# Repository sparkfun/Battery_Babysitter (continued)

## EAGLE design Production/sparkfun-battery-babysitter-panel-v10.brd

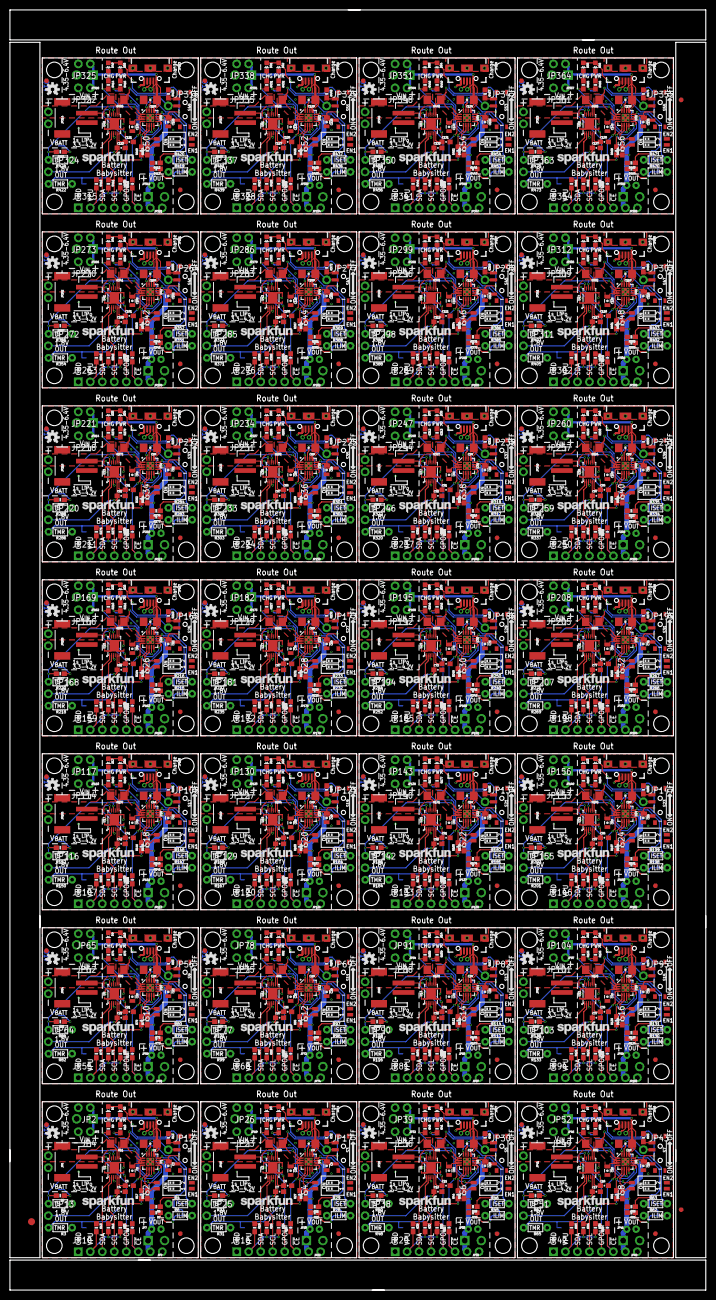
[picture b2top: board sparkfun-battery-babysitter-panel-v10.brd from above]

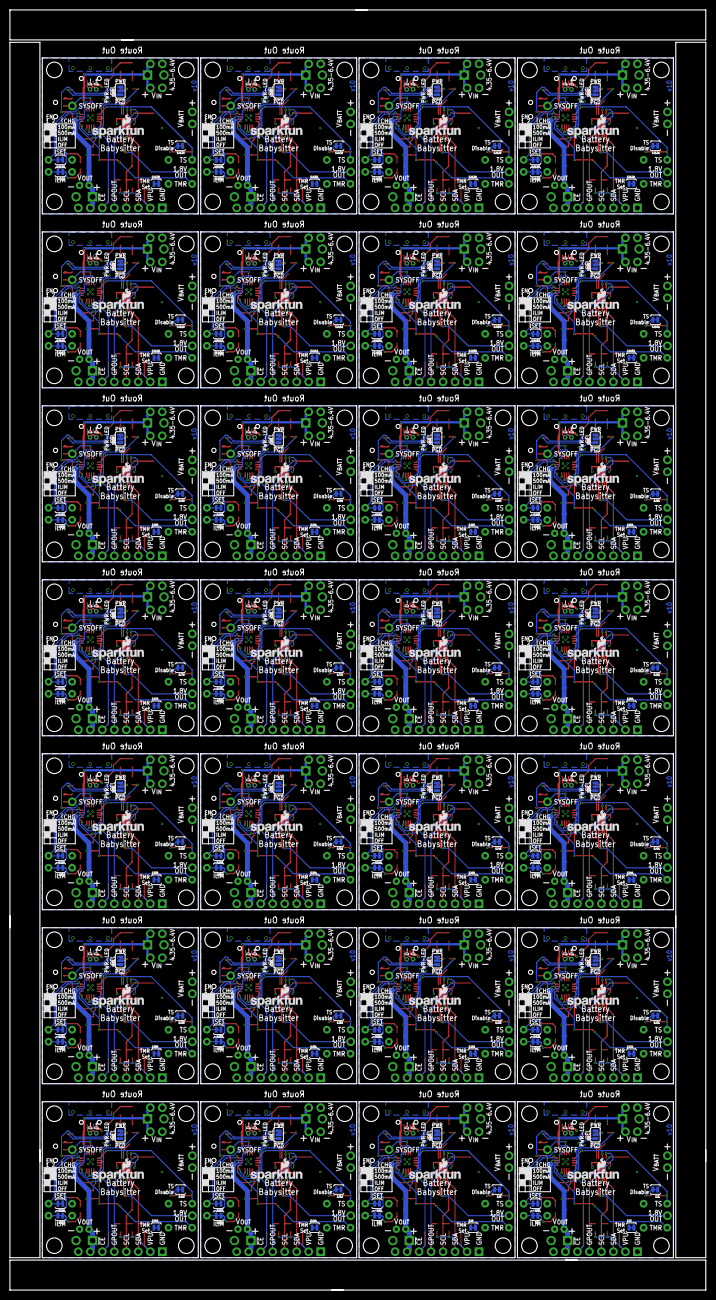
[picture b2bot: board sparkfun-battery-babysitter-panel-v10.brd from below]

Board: 2 copper layers, 147.3 x 271.0 mm, 1599 parts (224 on the bottom side), 840 nets.

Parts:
C1, C9, C14, C19, C24, C29, C34, C39, C44, C49, C54, C59, C64, C69, C74, C79, C84, C89, C94, C99, C104, C109, C114, C119, C124, C129, C134, C139: 1.0uF; 1206-CAP
C2, C3, C8, C10, C13, C15, C18, C20, C23, C25, C28, C30, C33, C35, C38, C40, C43, C45, C48, C50, C53, C55, C58, C60, C63, C65, C68, C70, C73, C75, C78, C80, C83, C85, C88, C90, C93, C95, C98, C100, C103, C105, C108, C110, C113, C115, C118, C120, C123, C125, C128, C130, C133, C135, C138, C140: 10uF; 0805-CAP
C4, C7, C12, C17, C22, C27, C32, C37, C42, C47, C52, C57, C62, C67, C72, C77, C82, C87, C92, C97, C102, C107, C112, C117, C122, C127, C132, C137: 0.47uF; 0603-CAP
C5, C6, C11, C16, C21, C26, C31, C36, C41, C46, C51, C56, C61, C66, C71, C76, C81, C86, C91, C96, C101, C106, C111, C116, C121, C126, C131, C136: 1.0uF; 0603-CAP
D1, D3, D5, D7, D9, D11, D13, D15, D17, D19, D21, D23, D25, D27, D29, D31, D33, D35, D37, D39, D41, D43, D45, D47, D49, D51, D53, D55: BLUE; LED-0603
D2, D4, D6, D8, D10, D12, D14, D16, D18, D20, D22, D24, D26, D28, D30, D32, D34, D36, D38, D40, D42, D44, D46, D48, D50, D52, D54, D56: RED; LED-0603
E$1: FIDUCIAL-1.5X3
E$5, E$6: FIDUCIAL-1X2
FID1, FID2, FID3, FID4, FID5, FID6, FID7, FID8, FID9, FID10, FID11, FID12, FID13, FID14, FID15, FID16, FID17, FID18, FID19, FID20, FID21, FID22, FID23, FID24, FID25, FID26, FID27, FID28, FID29, FID30, FID31, FID32, FID33, FID34, FID35, FID36, FID37, FID38, FID39, FID40, FID41, FID42, FID43, FID44, FID45, FID46, FID47, FID48, FID49, FID50, FID51, FID52, FID53, FID54, FID55, FID56: FIDUCIAL1X2; FIDUCIAL-1X2
JP1, JP14, JP27, JP40, JP53, JP66, JP79, JP92, JP105, JP118, JP131, JP144, JP157, JP170, JP183, JP196, JP209, JP222, JP235, JP248, JP261, JP274, JP287, JP300, JP313, JP326, JP339, JP352: USB-AB-MICRO-SMD_V03
JP2, JP4, JP5, JP8, JP11, JP18, JP21, JP23, JP24, JP26, JP31, JP34, JP36, JP37, JP39, JP44, JP47, JP49, JP50, JP52, JP57, JP60, JP62, JP63, JP65, JP70, JP73, JP75, JP76, JP78, JP83, JP86, JP88, JP89, JP91, JP96, JP99, JP101, JP102, JP104, JP109, JP112, JP114, JP115, JP117, JP122, JP125, JP127, JP128, JP130, JP135, JP138, JP140, JP141, JP143, JP148, JP151, JP153, JP154, JP156, JP161, JP164, JP166, JP167, JP169, JP174, JP177, JP179, JP180, JP182, JP187, JP190, JP192, JP193, JP195, JP200, JP203, JP205, JP206, JP208, JP213, JP216, JP218, JP219, JP221, JP226, JP229, JP231, JP232, JP234, JP239, JP242, JP244, JP245, JP247, JP252, JP255, JP257, JP258, JP260, JP265, JP268, JP270, JP271, JP273, JP278, JP281, JP283, JP284, JP286, JP291, JP294, JP296, JP297, JP299, JP304, JP307, JP309, JP310, JP312, JP317, JP320, JP322, JP323, JP325, JP330, JP333, JP335, JP336, JP338, JP343, JP346, JP348, JP349, JP351, JP356, JP359, JP361, JP362, JP364: 1X02_NO_SILK
JP3, JP7, JP19, JP20, JP32, JP33, JP45, JP46, JP58, JP59, JP71, JP72, JP84, JP85, JP97, JP98, JP110, JP111, JP123, JP124, JP136, JP137, JP149, JP150, JP162, JP163, JP175, JP176, JP188, JP189, JP201, JP202, JP214, JP215, JP227, JP228, JP240, JP241, JP253, JP254, JP266, JP267, JP279, JP280, JP292, JP293, JP305, JP306, JP318, JP319, JP331, JP332, JP344, JP345, JP357, JP358: SCREWTERMINAL-3.5MM-2-NS
JP6, JP15, JP28, JP41, JP54, JP67, JP80, JP93, JP106, JP119, JP132, JP145, JP158, JP171, JP184, JP197, JP210, JP223, JP236, JP249, JP262, JP275, JP288, JP301, JP314, JP327, JP340, JP353: JST-2-SMD
JP9, JP22, JP35, JP48, JP61, JP74, JP87, JP100, JP113, JP126, JP139, JP152, JP165, JP178, JP191, JP204, JP217, JP230, JP243, JP256, JP269, JP282, JP295, JP308, JP321, JP334, JP347, JP360: JST-2-PTH-NS
JP10, JP16, JP29, JP42, JP55, JP68, JP81, JP94, JP107, JP120, JP133, JP146, JP159, JP172, JP185, JP198, JP211, JP224, JP237, JP250, JP263, JP276, JP289, JP302, JP315, JP328, JP341, JP354: 1X04_NO_SILK
JP12, JP13, JP17, JP25, JP30, JP38, JP43, JP51, JP56, JP64, JP69, JP77, JP82, JP90, JP95, JP103, JP108, JP116, JP121, JP129, JP134, JP142, JP147, JP155, JP160, JP168, JP173, JP181, JP186, JP194, JP199, JP207, JP212, JP220, JP225, JP233, JP238, JP246, JP251, JP259, JP264, JP272, JP277, JP285, JP290, JP298, JP303, JP311, JP316, JP324, JP329, JP337, JP342, JP350, JP355, JP363: 1X01_NO_SILK
LOGO1, LOGO4, LOGO7, LOGO10, LOGO13, LOGO16, LOGO19, LOGO22, LOGO25, LOGO28, LOGO31, LOGO34, LOGO37, LOGO40, LOGO43, LOGO46, LOGO49, LOGO52, LOGO55, LOGO58, LOGO61, LOGO64, LOGO67, LOGO70, LOGO73, LOGO76, LOGO79, LOGO82: SFE_LOGO_NAME.1_INCH; SFE_LOGO_NAME_.1
LOGO2, LOGO6, LOGO9, LOGO12, LOGO15, LOGO18, LOGO21, LOGO24, LOGO27, LOGO30, LOGO33, LOGO36, LOGO39, LOGO42, LOGO45, LOGO48, LOGO51, LOGO54, LOGO57, LOGO60, LOGO63, LOGO66, LOGO69, LOGO72, LOGO75, LOGO78, LOGO81, LOGO84: SFE_LOGO_NAME_FLAME.1_INCH; SFE_LOGO_NAME_FLAME_.1
LOGO3, LOGO5, LOGO8, LOGO11, LOGO14, LOGO17, LOGO20, LOGO23, LOGO26, LOGO29, LOGO32, LOGO35, LOGO38, LOGO41, LOGO44, LOGO47, LOGO50, LOGO53, LOGO56, LOGO59, LOGO62, LOGO65, LOGO68, LOGO71, LOGO74, LOGO77, LOGO80, LOGO83: OSHW-LOGOS; OSHW-LOGO-S
R1, R33, R50, R67, R84, R101, R118, R135, R152, R169, R186, R203, R220, R237, R254, R271, R288, R305, R322, R339, R356, R373, R390, R407, R424, R441, R458, R475: TS; 1/6W-RES
R2, R15, R16, R17, R26, R27, R30, R34, R43, R44, R47, R51, R60, R61, R64, R68, R77, R78, R81, R85, R94, R95, R98, R102, R111, R112, R115, R119, R128, R129, R132, R136, R145, R146, R149, R153, R162, R163, R166, R170, R179, R180, R183, R187, R196, R197, R200, R204, R213, R214, R217, R221, R230, R231, R234, R238, R247, R248, R251, R255, R264, R265, R268, R272, R281, R282, R285, R289, R298, R299, R302, R306, R315, R316, R319, R323, R332, R333, R336, R340, R349, R350, R353, R357, R366, R367, R370, R374, R383, R384, R387, R391, R400, R401, R404, R408, R417, R418, R421, R425, R434, R435, R438, R442, R451, R452, R455, R459, R468, R469, R472, R476: 10K; 0603-RES
R3, R31, R48, R65, R82, R99, R116, R133, R150, R167, R184, R201, R218, R235, R252, R269, R286, R303, R320, R337, R354, R371, R388, R405, R422, R439, R456, R473: TMR; 1/6W-RES
R4, R29, R46, R63, R80, R97, R114, R131, R148, R165, R182, R199, R216, R233, R250, R267, R284, R301, R318, R335, R352, R369, R386, R403, R420, R437, R454, R471: ISET; 1/6W-RES
R5, R21, R38, R55, R72, R89, R106, R123, R140, R157, R174, R191, R208, R225, R242, R259, R276, R293, R310, R327, R344, R361, R378, R395, R412, R429, R446, R463: 590; 0603-RES
R6, R28, R45, R62, R79, R96, R113, R130, R147, R164, R181, R198, R215, R232, R249, R266, R283, R300, R317, R334, R351, R368, R385, R402, R419, R436, R453, R470: ILIM; 1/6W-RES
R7, R22, R39, R56, R73, R90, R107, R124, R141, R158, R175, R192, R209, R226, R243, R260, R277, R294, R311, R328, R345, R362, R379, R396, R413, R430, R447, R464: 1.1k; 0603-RES
R8, R12, R25, R32, R42, R49, R59, R66, R76, R83, R93, R100, R110, R117, R127, R134, R144, R151, R161, R168, R178, R185, R195, R202, R212, R219, R229, R236, R246, R253, R263, R270, R280, R287, R297, R304, R314, R321, R331, R338, R348, R355, R365, R372, R382, R389, R399, R406, R416, R423, R433, R440, R450, R457, R467, R474: 100k; 0603-RES
R9, R23, R40, R57, R74, R91, R108, R125, R142, R159, R176, R193, R210, R227, R244, R261, R278, R295, R312, R329, R346, R363, R380, R397, R414, R431, R448, R465: 180; 0603-RES
R10, R24, R41, R58, R75, R92, R109, R126, R143, R160, R177, R194, R211, R228, R245, R262, R279, R296, R313, R330, R347, R364, R381, R398, R415, R432, R449, R466: 1K; 0603-RES
R11, R18, R35, R52, R69, R86, R103, R120, R137, R154, R171, R188, R205, R222, R239, R256, R273, R290, R307, R324, R341, R358, R375, R392, R409, R426, R443, R460: 0.01; 1206
R13, R14, R19, R20, R36, R37, R53, R54, R70, R71, R87, R88, R104, R105, R121, R122, R138, R139, R155, R156, R172, R173, R189, R190, R206, R207, R223, R224, R240, R241, R257, R258, R274, R275, R291, R292, R308, R309, R325, R326, R342, R343, R359, R360, R376, R377, R393, R394, R410, R411, R427, R428, R444, R445, R461, R462: 4.7K; 0603-RES
S1, S3, S5, S7, S9, S11, S13, S15, S17, S19, S21, S23, S25, S27, S29, S31, S33, S35, S37, S39, S41, S43, S45, S47, S49, S51, S53, S55: SWITCH-SPST-SMD-A
S2, S4, S6, S8, S10, S12, S14, S16, S18, S20, S22, S24, S26, S28, S30, S32, S34, S36, S38, S40, S42, S44, S46, S48, S50, S52, S54, S56: DIPSWITCH-02-50MIL
SJ1, SJ2, SJ3, SJ4, SJ6, SJ7, SJ8, SJ9, SJ11, SJ12, SJ13, SJ14, SJ16, SJ17, SJ18, SJ19, SJ21, SJ22, SJ23, SJ24, SJ26, SJ27, SJ28, SJ29, SJ31, SJ32, SJ33, SJ34, SJ36, SJ37, SJ38, SJ39, SJ41, SJ42, SJ43, SJ44, SJ46, SJ47, SJ48, SJ49, SJ51, SJ52, SJ53, SJ54, SJ56, SJ57, SJ58, SJ59, SJ61, SJ62, SJ63, SJ64, SJ66, SJ67, SJ68, SJ69, SJ71, SJ72, SJ73, SJ74, SJ76, SJ77, SJ78, SJ79, SJ81, SJ82, SJ83, SJ84, SJ86, SJ87, SJ88, SJ89, SJ91, SJ92, SJ93, SJ94, SJ96, SJ97, SJ98, SJ99, SJ101, SJ102, SJ103, SJ104, SJ106, SJ107, SJ108, SJ109, SJ111, SJ112, SJ113, SJ114, SJ116, SJ117, SJ118, SJ119, SJ121, SJ122, SJ123, SJ124, SJ126, SJ127, SJ128, SJ129, SJ131, SJ132, SJ133, SJ134, SJ136, SJ137, SJ138, SJ139: PAD-JUMPER-2-NC_BY_TRACE_YES_SILK
SJ5, SJ10, SJ15, SJ20, SJ25, SJ30, SJ35, SJ40, SJ45, SJ50, SJ55, SJ60, SJ65, SJ70, SJ75, SJ80, SJ85, SJ90, SJ95, SJ100, SJ105, SJ110, SJ115, SJ120, SJ125, SJ130, SJ135, SJ140: PAD-JUMPER-3-2OF3_NC_BY_TRACE_YES_SILK_FULL_BOX
STANDOFF1, STANDOFF2, STANDOFF3, STANDOFF4, STANDOFF5, STANDOFF6, STANDOFF7, STANDOFF8, STANDOFF9, STANDOFF10, STANDOFF11, STANDOFF12, STANDOFF13, STANDOFF14, STANDOFF15, STANDOFF16, STANDOFF17, STANDOFF18, STANDOFF19, STANDOFF20, STANDOFF21, STANDOFF22, STANDOFF23, STANDOFF24, STANDOFF25, STANDOFF26, STANDOFF27, STANDOFF28, STANDOFF29, STANDOFF30, STANDOFF31, STANDOFF32, STANDOFF33, STANDOFF34, STANDOFF35, STANDOFF36, STANDOFF37, STANDOFF38, STANDOFF39, STANDOFF40, STANDOFF41, STANDOFF42, STANDOFF43, STANDOFF44, STANDOFF45, STANDOFF46, STANDOFF47, STANDOFF48, STANDOFF49, STANDOFF50, STANDOFF51, STANDOFF52, STANDOFF53, STANDOFF54, STANDOFF55, STANDOFF56, STANDOFF57, STANDOFF58, STANDOFF59, STANDOFF60, STANDOFF61, STANDOFF62, STANDOFF63, STANDOFF64, STANDOFF65, STANDOFF66, STANDOFF67, STANDOFF68, STANDOFF69, STANDOFF70, STANDOFF71, STANDOFF72, STANDOFF73, STANDOFF74, STANDOFF75, STANDOFF76, STANDOFF77, STANDOFF78, STANDOFF79, STANDOFF80, STANDOFF81, STANDOFF82, STANDOFF83, STANDOFF84, STANDOFF85, STANDOFF86, STANDOFF87, STANDOFF88, STANDOFF89, STANDOFF90, STANDOFF91, STANDOFF92, STANDOFF93, STANDOFF94, STANDOFF95, STANDOFF96, STANDOFF97, STANDOFF98, STANDOFF99, STANDOFF100, STANDOFF101, STANDOFF102, STANDOFF103, STANDOFF104, STANDOFF105, STANDOFF106, STANDOFF107, STANDOFF108, STANDOFF109, STANDOFF110, STANDOFF111, STANDOFF112: STAND-OFF
TP1, TP2, TP3, TP4, TP5, TP6, TP7, TP8, TP9, TP10, TP11, TP12, TP13, TP14, TP15, TP16, TP17, TP18, TP19, TP20, TP21, TP22, TP23, TP24, TP25, TP26, TP27, TP28, TP29, TP30, TP31, TP32, TP33, TP34, TP35, TP36, TP37, TP38, TP39, TP40, TP41, TP42, TP43, TP44, TP45, TP46, TP47, TP48, TP49, TP50, TP51, TP52, TP53, TP54, TP55, TP56: PAD.03X.04
U1, U4, U6, U8, U10, U12, U14, U16, U18, U20, U22, U24, U26, U28, U30, U32, U34, U36, U38, U40, U42, U44, U46, U48, U50, U52, U54, U56: BQ24075; PVQFN-N16
U2, U3, U5, U7, U9, U11, U13, U15, U17, U19, U21, U23, U25, U27, U29, U31, U33, U35, U37, U39, U41, U43, U45, U47, U49, U51, U53, U55: BQ27441-G1; PDSO-N12

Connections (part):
1.8V: C4.1, JP13.1, U2.5
1.8V1: C7.1, JP25.1, U3.5
1.8V2: C12.1, JP38.1, U5.5
1.8V3: C17.1, JP51.1, U7.5
1.8V4: C22.1, JP64.1, U9.5
1.8V5: C27.1, JP77.1, U11.5
1.8V6: C32.1, JP90.1, U13.5
1.8V7: C37.1, JP103.1, U15.5
1.8V8: C42.1, JP116.1, U17.5
1.8V9: C47.1, JP129.1, U19.5
1.8V10: C52.1, JP142.1, U21.5
1.8V11: C57.1, JP155.1, U23.5
1.8V12: C62.1, JP168.1, U25.5
1.8V13: C67.1, JP181.1, U27.5
1.8V14: C72.1, JP194.1, U29.5
1.8V15: C77.1, JP207.1, U31.5
1.8V16: C82.1, JP220.1, U33.5
1.8V17: C87.1, JP233.1, U35.5
1.8V18: C92.1, JP246.1, U37.5
1.8V19: C97.1, JP259.1, U39.5
1.8V20: C102.1, JP272.1, U41.5
1.8V21: C107.1, JP285.1, U43.5
1.8V22: C112.1, JP298.1, U45.5
1.8V23: C117.1, JP311.1, U47.5
1.8V24: C122.1, JP324.1, U49.5
1.8V25: C127.1, JP337.1, U51.5
1.8V26: C132.1, JP350.1, U53.5
1.8V27: C137.1, JP363.1, U55.5
!CE!: JP11.1, R8.1, U1.4
!CE!1: JP24.1, R25.1, U4.4
!CE!2: JP37.1, R42.1, U6.4
!CE!3: JP50.1, R59.1, U8.4
!CE!4: JP63.1, R76.1, U10.4
!CE!5: JP76.1, R93.1, U12.4
!CE!6: JP89.1, R110.1, U14.4
!CE!7: JP102.1, R127.1, U16.4
!CE!8: JP115.1, R144.1, U18.4
!CE!9: JP128.1, R161.1, U20.4
!CE!10: JP141.1, R178.1, U22.4
!CE!11: JP154.1, R195.1, U24.4
!CE!12: JP167.1, R212.1, U26.4
!CE!13: JP180.1, R229.1, U28.4
!CE!14: JP193.1, R246.1, U30.4
!CE!15: JP206.1, R263.1, U32.4
!CE!16: JP219.1, R280.1, U34.4
!CE!17: JP232.1, R297.1, U36.4
!CE!18: JP245.1, R314.1, U38.4
!CE!19: JP258.1, R331.1, U40.4
!CE!20: JP271.1, R348.1, U42.4
!CE!21: JP284.1, R365.1, U44.4
!CE!22: JP297.1, R382.1, U46.4
!CE!23: JP310.1, R399.1, U48.4
!CE!24: JP323.1, R416.1, U50.4
!CE!25: JP336.1, R433.1, U52.4
!CE!26: JP349.1, R450.1, U54.4
!CE!27: JP362.1, R467.1, U56.4
!CHG!: R9.2, U1.9
!CHG!1: R23.2, U4.9
!CHG!2: R40.2, U6.9
!CHG!3: R57.2, U8.9
!CHG!4: R74.2, U10.9
!CHG!5: R91.2, U12.9
!CHG!6: R108.2, U14.9
!CHG!7: R125.2, U16.9
!CHG!8: R142.2, U18.9
!CHG!9: R159.2, U20.9
!CHG!10: R176.2, U22.9
!CHG!11: R193.2, U24.9
!CHG!12: R210.2, U26.9
!CHG!13: R227.2, U28.9
!CHG!14: R244.2, U30.9
!CHG!15: R261.2, U32.9
!CHG!16: R278.2, U34.9
!CHG!17: R295.2, U36.9
!CHG!18: R312.2, U38.9
!CHG!19: R329.2, U40.9
!CHG!20: R346.2, U42.9
!CHG!21: R363.2, U44.9
!CHG!22: R380.2, U46.9
!CHG!23: R397.2, U48.9
!CHG!24: R414.2, U50.9
!CHG!25: R431.2, U52.9
!CHG!26: R448.2, U54.9
!CHG!27: R465.2, U56.9
!PGOOD!: SJ5.1, U1.7
!PGOOD!1: SJ10.1, U4.7
!PGOOD!2: SJ15.1, U6.7
!PGOOD!3: SJ20.1, U8.7
!PGOOD!4: SJ25.1, U10.7
!PGOOD!5: SJ30.1, U12.7
!PGOOD!6: SJ35.1, U14.7
!PGOOD!7: SJ40.1, U16.7
!PGOOD!8: SJ45.1, U18.7
!PGOOD!9: SJ50.1, U20.7
!PGOOD!10: SJ55.1, U22.7
!PGOOD!11: SJ60.1, U24.7
!PGOOD!12: SJ65.1, U26.7
!PGOOD!13: SJ70.1, U28.7
!PGOOD!14: SJ75.1, U30.7
!PGOOD!15: SJ80.1, U32.7
!PGOOD!16: SJ85.1, U34.7
!PGOOD!17: SJ90.1, U36.7
!PGOOD!18: SJ95.1, U38.7
!PGOOD!19: SJ100.1, U40.7
!PGOOD!20: SJ105.1, U42.7
!PGOOD!21: SJ110.1, U44.7
!PGOOD!22: SJ115.1, U46.7
!PGOOD!23: SJ120.1, U48.7
!PGOOD!24: SJ125.1, U50.7
!PGOOD!25: SJ130.1, U52.7
!PGOOD!26: SJ135.1, U54.7
!PGOOD!27: SJ140.1, U56.7
BATTERY_IN: C5.1, JP5.2, JP6.2, R11.2, U2.6, U2.8
BATTERY_IN1: C6.1, JP15.2, JP18.2, R18.2, U3.6, U3.8
BATTERY_IN2: C11.1, JP28.2, JP31.2, R35.2, U5.6, U5.8
BATTERY_IN3: C16.1, JP41.2, JP44.2, R52.2, U7.6, U7.8
BATTERY_IN4: C21.1, JP54.2, JP57.2, R69.2, U9.6, U9.8
BATTERY_IN5: C26.1, JP67.2, JP70.2, R86.2, U11.6, U11.8
BATTERY_IN6: C31.1, JP80.2, JP83.2, R103.2, U13.6, U13.8
BATTERY_IN7: C36.1, JP93.2, JP96.2, R120.2, U15.6, U15.8
BATTERY_IN8: C41.1, JP106.2, JP109.2, R137.2, U17.6, U17.8
BATTERY_IN9: C46.1, JP119.2, JP122.2, R154.2, U19.6, U19.8
BATTERY_IN10: C51.1, JP132.2, JP135.2, R171.2, U21.6, U21.8
BATTERY_IN11: C56.1, JP145.2, JP148.2, R188.2, U23.6, U23.8
BATTERY_IN12: C61.1, JP158.2, JP161.2, R205.2, U25.6, U25.8
BATTERY_IN13: C66.1, JP171.2, JP174.2, R222.2, U27.6, U27.8
BATTERY_IN14: C71.1, JP184.2, JP187.2, R239.2, U29.6, U29.8
BATTERY_IN15: C76.1, JP197.2, JP200.2, R256.2, U31.6, U31.8
BATTERY_IN16: C81.1, JP210.2, JP213.2, R273.2, U33.6, U33.8
BATTERY_IN17: C86.1, JP223.2, JP226.2, R290.2, U35.6, U35.8
BATTERY_IN18: C91.1, JP236.2, JP239.2, R307.2, U37.6, U37.8
BATTERY_IN19: C96.1, JP249.2, JP252.2, R324.2, U39.6, U39.8
BATTERY_IN20: C101.1, JP262.2, JP265.2, R341.2, U41.6, U41.8
BATTERY_IN21: C106.1, JP275.2, JP278.2, R358.2, U43.6, U43.8
BATTERY_IN22: C111.1, JP288.2, JP291.2, R375.2, U45.6, U45.8
BATTERY_IN23: C116.1, JP301.2, JP304.2, R392.2, U47.6, U47.8
BATTERY_IN24: C121.1, JP314.2, JP317.2, R409.2, U49.6, U49.8
BATTERY_IN25: C126.1, JP327.2, JP330.2, R426.2, U51.6, U51.8
BATTERY_IN26: C131.1, JP340.2, JP343.2, R443.2, U53.6, U53.8
BATTERY_IN27: C136.1, JP353.2, JP356.2, R460.2, U55.6, U55.8
D+: JP1.D+1, TP2.P$1
D+1: JP14.D+1, TP4.P$1
D+2: JP27.D+1, TP6.P$1
D+3: JP40.D+1, TP8.P$1
D+4: JP53.D+1, TP10.P$1
D+5: JP66.D+1, TP12.P$1
D+6: JP79.D+1, TP14.P$1
D+7: JP92.D+1, TP16.P$1
D+8: JP105.D+1, TP18.P$1
D+9: JP118.D+1, TP20.P$1
D+10: JP131.D+1, TP22.P$1
D+11: JP144.D+1, TP24.P$1
D+12: JP157.D+1, TP26.P$1
D+13: JP170.D+1, TP28.P$1
D+14: JP183.D+1, TP30.P$1
D+15: JP196.D+1, TP32.P$1
D+16: JP209.D+1, TP34.P$1
D+17: JP222.D+1, TP36.P$1
D+18: JP235.D+1, TP38.P$1
D+19: JP248.D+1, TP40.P$1
D+20: JP261.D+1, TP42.P$1
D+21: JP274.D+1, TP44.P$1
D+22: JP287.D+1, TP46.P$1
D+23: JP300.D+1, TP48.P$1
D+24: JP313.D+1, TP50.P$1
D+25: JP326.D+1, TP52.P$1
D+26: JP339.D+1, TP54.P$1
D+27: JP352.D+1, TP56.P$1
D-: JP1.D-1, TP1.P$1
D-1: JP14.D-1, TP3.P$1
D-2: JP27.D-1, TP5.P$1
D-3: JP40.D-1, TP7.P$1
D-4: JP53.D-1, TP9.P$1
D-5: JP66.D-1, TP11.P$1
D-6: JP79.D-1, TP13.P$1
D-7: JP92.D-1, TP15.P$1
D-8: JP105.D-1, TP17.P$1
D-9: JP118.D-1, TP19.P$1
D-10: JP131.D-1, TP21.P$1
D-11: JP144.D-1, TP23.P$1
D-12: JP157.D-1, TP25.P$1
D-13: JP170.D-1, TP27.P$1
D-14: JP183.D-1, TP29.P$1
D-15: JP196.D-1, TP31.P$1
D-16: JP209.D-1, TP33.P$1
D-17: JP222.D-1, TP35.P$1
D-18: JP235.D-1, TP37.P$1
D-19: JP248.D-1, TP39.P$1
D-20: JP261.D-1, TP41.P$1
D-21: JP274.D-1, TP43.P$1
D-22: JP287.D-1, TP45.P$1
D-23: JP300.D-1, TP47.P$1
D-24: JP313.D-1, TP49.P$1
D-25: JP326.D-1, TP51.P$1
D-26: JP339.D-1, TP53.P$1
D-27: JP352.D-1, TP55.P$1
EN1: R16.2, S2.4, U1.6
EN2: R17.2, S2.3, U1.5
EN3: R27.2, S4.3, U4.5
EN4: R26.2, S4.4, U4.6
EN5: R44.2, S6.3, U6.5
EN6: R43.2, S6.4, U6.6
EN7: R61.2, S8.3, U8.5
EN8: R60.2, S8.4, U8.6
EN9: R78.2, S10.3, U10.5
EN10: R77.2, S10.4, U10.6
EN11: R95.2, S12.3, U12.5
EN12: R94.2, S12.4, U12.6
EN13: R112.2, S14.3, U14.5
EN14: R111.2, S14.4, U14.6
EN15: R129.2, S16.3, U16.5
EN16: R128.2, S16.4, U16.6
EN17: R146.2, S18.3, U18.5
EN18: R145.2, S18.4, U18.6
EN19: R163.2, S20.3, U20.5
EN20: R162.2, S20.4, U20.6
EN21: R180.2, S22.3, U22.5
EN22: R179.2, S22.4, U22.6
EN23: R197.2, S24.3, U24.5
EN24: R196.2, S24.4, U24.6
EN25: R214.2, S26.3, U26.5
EN26: R213.2, S26.4, U26.6
EN27: R231.2, S28.3, U28.5
EN28: R230.2, S28.4, U28.6
EN29: R248.2, S30.3, U30.5
EN30: R247.2, S30.4, U30.6
EN31: R265.2, S32.3, U32.5
EN32: R264.2, S32.4, U32.6
EN33: R282.2, S34.3, U34.5
EN34: R281.2, S34.4, U34.6
EN35: R299.2, S36.3, U36.5
EN36: R298.2, S36.4, U36.6
EN37: R316.2, S38.3, U38.5
EN38: R315.2, S38.4, U38.6
EN39: R333.2, S40.3, U40.5
EN40: R332.2, S40.4, U40.6
EN41: R350.2, S42.3, U42.5
EN42: R349.2, S42.4, U42.6
EN43: R367.2, S44.3, U44.5
EN44: R366.2, S44.4, U44.6
EN45: R384.2, S46.3, U46.5
EN46: R383.2, S46.4, U46.6
EN47: R401.2, S48.3, U48.5
EN48: R400.2, S48.4, U48.6
EN49: R418.2, S50.3, U50.5
EN50: R417.2, S50.4, U50.6
EN51: R435.2, S52.3, U52.5
EN52: R434.2, S52.4, U52.6
EN53: R452.2, S54.3, U54.5
EN54: R451.2, S54.4, U54.6
EN55: R469.2, S56.3, U56.5
EN56: R468.2, S56.4, U56.6
GND: C1.2, C2.2, C3.2, C4.2, C5.2, JP1.GND1, JP2.2, JP3.2, JP4.2, JP5.1, JP6.1, JP7.2, JP8.1, JP9.1, JP10.1, R1.1, R3.1, R4.1, R5.2, R6.1, R7.2, R8.2, S1.3, S2.1, S2.2, SJ1.1, SJ2.1, SJ5.3, U1.8, U1.EP, U2.3, U2.EP, U2.EP1, U2.EP2, U2.EP3, U2.EP4
GND1: C6.2, C7.2, C8.2, C9.2, C10.2, JP14.GND1, JP15.1, JP16.1, JP18.1, JP19.2, JP20.2, JP21.1, JP22.1, JP23.2, JP26.2, R21.2, R22.2, R25.2, R28.1, R29.1, R31.1, R33.1, S3.3, S4.1, S4.2, SJ6.1, SJ9.1, SJ10.3, U3.3, U3.EP, U3.EP1, U3.EP2, U3.EP3, U3.EP4, U4.8, U4.EP
GND2: C11.2, C12.2, C13.2, C14.2, C15.2, JP27.GND1, JP28.1, JP29.1, JP31.1, JP32.2, JP33.2, JP34.1, JP35.1, JP36.2, JP39.2, R38.2, R39.2, R42.2, R45.1, R46.1, R48.1, R50.1, S5.3, S6.1, S6.2, SJ11.1, SJ14.1, SJ15.3, U5.3, U5.EP, U5.EP1, U5.EP2, U5.EP3, U5.EP4, U6.8, U6.EP
GND3: C16.2, C17.2, C18.2, C19.2, C20.2, JP40.GND1, JP41.1, JP42.1, JP44.1, JP45.2, JP46.2, JP47.1, JP48.1, JP49.2, JP52.2, R55.2, R56.2, R59.2, R62.1, R63.1, R65.1, R67.1, S7.3, S8.1, S8.2, SJ16.1, SJ19.1, SJ20.3, U7.3, U7.EP, U7.EP1, U7.EP2, U7.EP3, U7.EP4, U8.8, U8.EP
GND4: C21.2, C22.2, C23.2, C24.2, C25.2, JP53.GND1, JP54.1, JP55.1, JP57.1, JP58.2, JP59.2, JP60.1, JP61.1, JP62.2, JP65.2, R72.2, R73.2, R76.2, R79.1, R80.1, R82.1, R84.1, S9.3, S10.1, S10.2, SJ21.1, SJ24.1, SJ25.3, U9.3, U9.EP, U9.EP1, U9.EP2, U9.EP3, U9.EP4, U10.8, U10.EP
GND5: C26.2, C27.2, C28.2, C29.2, C30.2, JP66.GND1, JP67.1, JP68.1, JP70.1, JP71.2, JP72.2, JP73.1, JP74.1, JP75.2, JP78.2, R89.2, R90.2, R93.2, R96.1, R97.1, R99.1, R101.1, S11.3, S12.1, S12.2, SJ26.1, SJ29.1, SJ30.3, U11.3, U11.EP, U11.EP1, U11.EP2, U11.EP3, U11.EP4, U12.8, U12.EP
GND6: C31.2, C32.2, C33.2, C34.2, C35.2, JP79.GND1, JP80.1, JP81.1, JP83.1, JP84.2, JP85.2, JP86.1, JP87.1, JP88.2, JP91.2, R106.2, R107.2, R110.2, R113.1, R114.1, R116.1, R118.1, S13.3, S14.1, S14.2, SJ31.1, SJ34.1, SJ35.3, U13.3, U13.EP, U13.EP1, U13.EP2, U13.EP3, U13.EP4, U14.8, U14.EP
GND7: C36.2, C37.2, C38.2, C39.2, C40.2, JP92.GND1, JP93.1, JP94.1, JP96.1, JP97.2, JP98.2, JP99.1, JP100.1, JP101.2, JP104.2, R123.2, R124.2, R127.2, R130.1, R131.1, R133.1, R135.1, S15.3, S16.1, S16.2, SJ36.1, SJ39.1, SJ40.3, U15.3, U15.EP, U15.EP1, U15.EP2, U15.EP3, U15.EP4, U16.8, U16.EP
GND8: C41.2, C42.2, C43.2, C44.2, C45.2, JP105.GND1, JP106.1, JP107.1, JP109.1, JP110.2, JP111.2, JP112.1, JP113.1, JP114.2, JP117.2, R140.2, R141.2, R144.2, R147.1, R148.1, R150.1, R152.1, S17.3, S18.1, S18.2, SJ41.1, SJ44.1, SJ45.3, U17.3, U17.EP, U17.EP1, U17.EP2, U17.EP3, U17.EP4, U18.8, U18.EP
GND9: C46.2, C47.2, C48.2, C49.2, C50.2, JP118.GND1, JP119.1, JP120.1, JP122.1, JP123.2, JP124.2, JP125.1, JP126.1, JP127.2, JP130.2, R157.2, R158.2, R161.2, R164.1, R165.1, R167.1, R169.1, S19.3, S20.1, S20.2, SJ46.1, SJ49.1, SJ50.3, U19.3, U19.EP, U19.EP1, U19.EP2, U19.EP3, U19.EP4, U20.8, U20.EP
GND10: C51.2, C52.2, C53.2, C54.2, C55.2, JP131.GND1, JP132.1, JP133.1, JP135.1, JP136.2, JP137.2, JP138.1, JP139.1, JP140.2, JP143.2, R174.2, R175.2, R178.2, R181.1, R182.1, R184.1, R186.1, S21.3, S22.1, S22.2, SJ51.1, SJ54.1, SJ55.3, U21.3, U21.EP, U21.EP1, U21.EP2, U21.EP3, U21.EP4, U22.8, U22.EP
GND11: C56.2, C57.2, C58.2, C59.2, C60.2, JP144.GND1, JP145.1, JP146.1, JP148.1, JP149.2, JP150.2, JP151.1, JP152.1, JP153.2, JP156.2, R191.2, R192.2, R195.2, R198.1, R199.1, R201.1, R203.1, S23.3, S24.1, S24.2, SJ56.1, SJ59.1, SJ60.3, U23.3, U23.EP, U23.EP1, U23.EP2, U23.EP3, U23.EP4, U24.8, U24.EP
GND12: C61.2, C62.2, C63.2, C64.2, C65.2, JP157.GND1, JP158.1, JP159.1, JP161.1, JP162.2, JP163.2, JP164.1, JP165.1, JP166.2, JP169.2, R208.2, R209.2, R212.2, R215.1, R216.1, R218.1, R220.1, S25.3, S26.1, S26.2, SJ61.1, SJ64.1, SJ65.3, U25.3, U25.EP, U25.EP1, U25.EP2, U25.EP3, U25.EP4, U26.8, U26.EP
GND13: C66.2, C67.2, C68.2, C69.2, C70.2, JP170.GND1, JP171.1, JP172.1, JP174.1, JP175.2, JP176.2, JP177.1, JP178.1, JP179.2, JP182.2, R225.2, R226.2, R229.2, R232.1, R233.1, R235.1, R237.1, S27.3, S28.1, S28.2, SJ66.1, SJ69.1, SJ70.3, U27.3, U27.EP, U27.EP1, U27.EP2, U27.EP3, U27.EP4, U28.8, U28.EP
GND14: C71.2, C72.2, C73.2, C74.2, C75.2, JP183.GND1, JP184.1, JP185.1, JP187.1, JP188.2, JP189.2, JP190.1, JP191.1, JP192.2, JP195.2, R242.2, R243.2, R246.2, R249.1, R250.1, R252.1, R254.1, S29.3, S30.1, S30.2, SJ71.1, SJ74.1, SJ75.3, U29.3, U29.EP, U29.EP1, U29.EP2, U29.EP3, U29.EP4, U30.8, U30.EP
GND15: C76.2, C77.2, C78.2, C79.2, C80.2, JP196.GND1, JP197.1, JP198.1, JP200.1, JP201.2, JP202.2, JP203.1, JP204.1, JP205.2, JP208.2, R259.2, R260.2, R263.2, R266.1, R267.1, R269.1, R271.1, S31.3, S32.1, S32.2, SJ76.1, SJ79.1, SJ80.3, U31.3, U31.EP, U31.EP1, U31.EP2, U31.EP3, U31.EP4, U32.8, U32.EP
GND16: C81.2, C82.2, C83.2, C84.2, C85.2, JP209.GND1, JP210.1, JP211.1, JP213.1, JP214.2, JP215.2, JP216.1, JP217.1, JP218.2, JP221.2, R276.2, R277.2, R280.2, R283.1, R284.1, R286.1, R288.1, S33.3, S34.1, S34.2, SJ81.1, SJ84.1, SJ85.3, U33.3, U33.EP, U33.EP1, U33.EP2, U33.EP3, U33.EP4, U34.8, U34.EP
GND17: C86.2, C87.2, C88.2, C89.2, C90.2, JP222.GND1, JP223.1, JP224.1, JP226.1, JP227.2, JP228.2, JP229.1, JP230.1, JP231.2, JP234.2, R293.2, R294.2, R297.2, R300.1, R301.1, R303.1, R305.1, S35.3, S36.1, S36.2, SJ86.1, SJ89.1, SJ90.3, U35.3, U35.EP, U35.EP1, U35.EP2, U35.EP3, U35.EP4, U36.8, U36.EP
GND18: C91.2, C92.2, C93.2, C94.2, C95.2, JP235.GND1, JP236.1, JP237.1, JP239.1, JP240.2, JP241.2, JP242.1, JP243.1, JP244.2, JP247.2, R310.2, R311.2, R314.2, R317.1, R318.1, R320.1, R322.1, S37.3, S38.1, S38.2, SJ91.1, SJ94.1, SJ95.3, U37.3, U37.EP, U37.EP1, U37.EP2, U37.EP3, U37.EP4, U38.8, U38.EP
GND19: C96.2, C97.2, C98.2, C99.2, C100.2, JP248.GND1, JP249.1, JP250.1, JP252.1, JP253.2, JP254.2, JP255.1, JP256.1, JP257.2, JP260.2, R327.2, R328.2, R331.2, R334.1, R335.1, R337.1, R339.1, S39.3, S40.1, S40.2, SJ96.1, SJ99.1, SJ100.3, U39.3, U39.EP, U39.EP1, U39.EP2, U39.EP3, U39.EP4, U40.8, U40.EP
GND20: C101.2, C102.2, C103.2, C104.2, C105.2, JP261.GND1, JP262.1, JP263.1, JP265.1, JP266.2, JP267.2, JP268.1, JP269.1, JP270.2, JP273.2, R344.2, R345.2, R348.2, R351.1, R352.1, R354.1, R356.1, S41.3, S42.1, S42.2, SJ101.1, SJ104.1, SJ105.3, U41.3, U41.EP, U41.EP1, U41.EP2, U41.EP3, U41.EP4, U42.8, U42.EP
GND21: C106.2, C107.2, C108.2, C109.2, C110.2, JP274.GND1, JP275.1, JP276.1, JP278.1, JP279.2, JP280.2, JP281.1, JP282.1, JP283.2, JP286.2, R361.2, R362.2, R365.2, R368.1, R369.1, R371.1, R373.1, S43.3, S44.1, S44.2, SJ106.1, SJ109.1, SJ110.3, U43.3, U43.EP, U43.EP1, U43.EP2, U43.EP3, U43.EP4, U44.8, U44.EP
GND22: C111.2, C112.2, C113.2, C114.2, C115.2, JP287.GND1, JP288.1, JP289.1, JP291.1, JP292.2, JP293.2, JP294.1, JP295.1, JP296.2, JP299.2, R378.2, R379.2, R382.2, R385.1, R386.1, R388.1, R390.1, S45.3, S46.1, S46.2, SJ111.1, SJ114.1, SJ115.3, U45.3, U45.EP, U45.EP1, U45.EP2, U45.EP3, U45.EP4, U46.8, U46.EP
GND23: C116.2, C117.2, C118.2, C119.2, C120.2, JP300.GND1, JP301.1, JP302.1, JP304.1, JP305.2, JP306.2, JP307.1, JP308.1, JP309.2, JP312.2, R395.2, R396.2, R399.2, R402.1, R403.1, R405.1, R407.1, S47.3, S48.1, S48.2, SJ116.1, SJ119.1, SJ120.3, U47.3, U47.EP, U47.EP1, U47.EP2, U47.EP3, U47.EP4, U48.8, U48.EP
GND24: C121.2, C122.2, C123.2, C124.2, C125.2, JP313.GND1, JP314.1, JP315.1, JP317.1, JP318.2, JP319.2, JP320.1, JP321.1, JP322.2, JP325.2, R412.2, R413.2, R416.2, R419.1, R420.1, R422.1, R424.1, S49.3, S50.1, S50.2, SJ121.1, SJ124.1, SJ125.3, U49.3, U49.EP, U49.EP1, U49.EP2, U49.EP3, U49.EP4, U50.8, U50.EP
GND25: C126.2, C127.2, C128.2, C129.2, C130.2, JP326.GND1, JP327.1, JP328.1, JP330.1, JP331.2, JP332.2, JP333.1, JP334.1, JP335.2, JP338.2, R429.2, R430.2, R433.2, R436.1, R437.1, R439.1, R441.1, S51.3, S52.1, S52.2, SJ126.1, SJ129.1, SJ130.3, U51.3, U51.EP, U51.EP1, U51.EP2, U51.EP3, U51.EP4, U52.8, U52.EP
GND26: C131.2, C132.2, C133.2, C134.2, C135.2, JP339.GND1, JP340.1, JP341.1, JP343.1, JP344.2, JP345.2, JP346.1, JP347.1, JP348.2, JP351.2, R446.2, R447.2, R450.2, R453.1, R454.1, R456.1, R458.1, S53.3, S54.1, S54.2, SJ131.1, SJ134.1, SJ135.3, U53.3, U53.EP, U53.EP1, U53.EP2, U53.EP3, U53.EP4, U54.8, U54.EP
GND27: C136.2, C137.2, C138.2, C139.2, C140.2, JP352.GND1, JP353.1, JP354.1, JP356.1, JP357.2, JP358.2, JP359.1, JP360.1, JP361.2, JP364.2, R463.2, R464.2, R467.2, R470.1, R471.1, R473.1, R475.1, S55.3, S56.1, S56.2, SJ136.1, SJ139.1, SJ140.3, U55.3, U55.EP, U55.EP1, U55.EP2, U55.EP3, U55.EP4, U56.8, U56.EP
GPOUT: JP11.2, R15.1, U2.12
GPOUT1: JP24.2, R34.1, U3.12
GPOUT2: JP37.2, R51.1, U5.12
GPOUT3: JP50.2, R68.1, U7.12
GPOUT4: JP63.2, R85.1, U9.12
GPOUT5: JP76.2, R102.1, U11.12
GPOUT6: JP89.2, R119.1, U13.12
GPOUT7: JP102.2, R136.1, U15.12
GPOUT8: JP115.2, R153.1, U17.12
GPOUT9: JP128.2, R170.1, U19.12
GPOUT10: JP141.2, R187.1, U21.12
GPOUT11: JP154.2, R204.1, U23.12
GPOUT12: JP167.2, R221.1, U25.12
GPOUT13: JP180.2, R238.1, U27.12
GPOUT14: JP193.2, R255.1, U29.12
GPOUT15: JP206.2, R272.1, U31.12
GPOUT16: JP219.2, R289.1, U33.12
GPOUT17: JP232.2, R306.1, U35.12
GPOUT18: JP245.2, R323.1, U37.12
GPOUT19: JP258.2, R340.1, U39.12
GPOUT20: JP271.2, R357.1, U41.12
GPOUT21: JP284.2, R374.1, U43.12
GPOUT22: JP297.2, R391.1, U45.12
GPOUT23: JP310.2, R408.1, U47.12
GPOUT24: JP323.2, R425.1, U49.12
GPOUT25: JP336.2, R442.1, U51.12
GPOUT26: JP349.2, R459.1, U53.12
GPOUT27: JP362.2, R476.1, U55.12
ILIM: R6.2, SJ4.2, U1.12
ILIM1: R28.2, SJ7.2, U4.12
ILIM2: R45.2, SJ12.2, U6.12
ILIM3: R62.2, SJ17.2, U8.12
ILIM4: R79.2, SJ22.2, U10.12
ILIM5: R96.2, SJ27.2, U12.12
ILIM6: R113.2, SJ32.2, U14.12
ILIM7: R130.2, SJ37.2, U16.12
ILIM8: R147.2, SJ42.2, U18.12
ILIM9: R164.2, SJ47.2, U20.12
ILIM10: R181.2, SJ52.2, U22.12
ILIM11: R198.2, SJ57.2, U24.12
ILIM12: R215.2, SJ62.2, U26.12
ILIM13: R232.2, SJ67.2, U28.12
ILIM14: R249.2, SJ72.2, U30.12
ILIM15: R266.2, SJ77.2, U32.12
ILIM16: R283.2, SJ82.2, U34.12
ILIM17: R300.2, SJ87.2, U36.12
ILIM18: R317.2, SJ92.2, U38.12
ILIM19: R334.2, SJ97.2, U40.12
ILIM20: R351.2, SJ102.2, U42.12
ILIM21: R368.2, SJ107.2, U44.12
ILIM22: R385.2, SJ112.2, U46.12
ILIM23: R402.2, SJ117.2, U48.12
ILIM24: R419.2, SJ122.2, U50.12
ILIM25: R436.2, SJ127.2, U52.12
ILIM26: R453.2, SJ132.2, U54.12
ILIM27: R470.2, SJ137.2, U56.12
ISET: R4.2, SJ3.2, U1.16
ISET1: R29.2, SJ8.2, U4.16
ISET2: R46.2, SJ13.2, U6.16
ISET3: R63.2, SJ18.2, U8.16
ISET4: R80.2, SJ23.2, U10.16
ISET5: R97.2, SJ28.2, U12.16
ISET6: R114.2, SJ33.2, U14.16
ISET7: R131.2, SJ38.2, U16.16
ISET8: R148.2, SJ43.2, U18.16
ISET9: R165.2, SJ48.2, U20.16
ISET10: R182.2, SJ53.2, U22.16
ISET11: R199.2, SJ58.2, U24.16
ISET12: R216.2, SJ63.2, U26.16
ISET13: R233.2, SJ68.2, U28.16
ISET14: R250.2, SJ73.2, U30.16
ISET15: R267.2, SJ78.2, U32.16
ISET16: R284.2, SJ83.2, U34.16
ISET17: R301.2, SJ88.2, U36.16
ISET18: R318.2, SJ93.2, U38.16
ISET19: R335.2, SJ98.2, U40.16
ISET20: R352.2, SJ103.2, U42.16
ISET21: R369.2, SJ108.2, U44.16
ISET22: R386.2, SJ113.2, U46.16
ISET23: R403.2, SJ118.2, U48.16
ISET24: R420.2, SJ123.2, U50.16
ISET25: R437.2, SJ128.2, U52.16
ISET26: R454.2, SJ133.2, U54.16
ISET27: R471.2, SJ138.2, U56.16
unnamed: R2.1, SJ1.2
unnamed: R7.1, SJ4.1
unnamed: R5.1, SJ3.1
unnamed: R12.2, S1.1
unnamed: R10.2, SJ5.2
unnamed: D3.C, R23.1
unnamed: D4.C, R24.1
unnamed: R32.2, S3.1
unnamed: R30.1, SJ6.2
unnamed: R22.1, SJ7.1
unnamed: D1.C, R9.1
unnamed: D2.C, R10.1
unnamed: R21.1, SJ8.1
unnamed: R24.2, SJ10.2
unnamed: D5.C, R40.1
unnamed: D6.C, R41.1
unnamed: R49.2, S5.1
unnamed: R47.1, SJ11.2
unnamed: R39.1, SJ12.1
unnamed: R38.1, SJ13.1
unnamed: R41.2, SJ15.2
unnamed: D7.C, R57.1
unnamed: D8.C, R58.1
unnamed: R66.2, S7.1
unnamed: R64.1, SJ16.2
unnamed: R56.1, SJ17.1
unnamed: R55.1, SJ18.1
unnamed: R58.2, SJ20.2
unnamed: D9.C, R74.1
unnamed: D10.C, R75.1
unnamed: R83.2, S9.1
unnamed: R81.1, SJ21.2
unnamed: R73.1, SJ22.1
unnamed: R72.1, SJ23.1
unnamed: R75.2, SJ25.2
unnamed: D11.C, R91.1
unnamed: D12.C, R92.1
unnamed: R100.2, S11.1
unnamed: R98.1, SJ26.2
unnamed: R90.1, SJ27.1
unnamed: R89.1, SJ28.1
unnamed: R92.2, SJ30.2
unnamed: D13.C, R108.1
unnamed: D14.C, R109.1
unnamed: R117.2, S13.1
unnamed: R115.1, SJ31.2
unnamed: R107.1, SJ32.1
unnamed: R106.1, SJ33.1
unnamed: R109.2, SJ35.2
unnamed: D15.C, R125.1
unnamed: D16.C, R126.1
unnamed: R134.2, S15.1
unnamed: R132.1, SJ36.2
unnamed: R124.1, SJ37.1
unnamed: R123.1, SJ38.1
unnamed: R126.2, SJ40.2
unnamed: D17.C, R142.1
unnamed: D18.C, R143.1
unnamed: R151.2, S17.1
unnamed: R149.1, SJ41.2
unnamed: R141.1, SJ42.1
unnamed: R140.1, SJ43.1
unnamed: R143.2, SJ45.2
unnamed: D19.C, R159.1
unnamed: D20.C, R160.1
unnamed: R168.2, S19.1
unnamed: R166.1, SJ46.2
unnamed: R158.1, SJ47.1
unnamed: R157.1, SJ48.1
unnamed: R160.2, SJ50.2
unnamed: D21.C, R176.1
unnamed: D22.C, R177.1
unnamed: R185.2, S21.1
unnamed: R183.1, SJ51.2
unnamed: R175.1, SJ52.1
unnamed: R174.1, SJ53.1
unnamed: R177.2, SJ55.2
unnamed: D23.C, R193.1
unnamed: D24.C, R194.1
unnamed: R202.2, S23.1
unnamed: R200.1, SJ56.2
unnamed: R192.1, SJ57.1
unnamed: R191.1, SJ58.1
unnamed: R194.2, SJ60.2
unnamed: D25.C, R210.1
unnamed: D26.C, R211.1
unnamed: R219.2, S25.1
unnamed: R217.1, SJ61.2
unnamed: R209.1, SJ62.1
unnamed: R208.1, SJ63.1
unnamed: R211.2, SJ65.2
unnamed: D27.C, R227.1
unnamed: D28.C, R228.1
unnamed: R236.2, S27.1
unnamed: R234.1, SJ66.2
unnamed: R226.1, SJ67.1
unnamed: R225.1, SJ68.1
unnamed: R228.2, SJ70.2
unnamed: D29.C, R244.1
unnamed: D30.C, R245.1
unnamed: R253.2, S29.1
unnamed: R251.1, SJ71.2
unnamed: R243.1, SJ72.1
unnamed: R242.1, SJ73.1
unnamed: R245.2, SJ75.2
unnamed: D31.C, R261.1
unnamed: D32.C, R262.1
unnamed: R270.2, S31.1
unnamed: R268.1, SJ76.2
unnamed: R260.1, SJ77.1
unnamed: R259.1, SJ78.1
unnamed: R262.2, SJ80.2
unnamed: D33.C, R278.1
unnamed: D34.C, R279.1
unnamed: R287.2, S33.1
unnamed: R285.1, SJ81.2
unnamed: R277.1, SJ82.1
unnamed: R276.1, SJ83.1
unnamed: R279.2, SJ85.2
unnamed: D35.C, R295.1
unnamed: D36.C, R296.1
unnamed: R304.2, S35.1
unnamed: R302.1, SJ86.2
unnamed: R294.1, SJ87.1
unnamed: R293.1, SJ88.1
unnamed: R296.2, SJ90.2
unnamed: D37.C, R312.1
unnamed: D38.C, R313.1
unnamed: R321.2, S37.1
unnamed: R319.1, SJ91.2
unnamed: R311.1, SJ92.1
unnamed: R310.1, SJ93.1
unnamed: R313.2, SJ95.2
unnamed: D39.C, R329.1
unnamed: D40.C, R330.1
unnamed: R338.2, S39.1
unnamed: R336.1, SJ96.2
unnamed: R328.1, SJ97.1
unnamed: R327.1, SJ98.1
unnamed: R330.2, SJ100.2
unnamed: D41.C, R346.1
unnamed: D42.C, R347.1
unnamed: R355.2, S41.1
unnamed: R353.1, SJ101.2
unnamed: R345.1, SJ102.1
unnamed: R344.1, SJ103.1
unnamed: R347.2, SJ105.2
unnamed: D43.C, R363.1
unnamed: D44.C, R364.1
unnamed: R372.2, S43.1
unnamed: R370.1, SJ106.2
unnamed: R362.1, SJ107.1
unnamed: R361.1, SJ108.1
unnamed: R364.2, SJ110.2
unnamed: D45.C, R380.1
unnamed: D46.C, R381.1
unnamed: R389.2, S45.1
unnamed: R387.1, SJ111.2
unnamed: R379.1, SJ112.1
unnamed: R378.1, SJ113.1
unnamed: R381.2, SJ115.2
unnamed: D47.C, R397.1
unnamed: D48.C, R398.1
unnamed: R406.2, S47.1
unnamed: R404.1, SJ116.2
unnamed: R396.1, SJ117.1
unnamed: R395.1, SJ118.1
unnamed: R398.2, SJ120.2
unnamed: D49.C, R414.1
unnamed: D50.C, R415.1
unnamed: R423.2, S49.1
unnamed: R421.1, SJ121.2
unnamed: R413.1, SJ122.1
unnamed: R412.1, SJ123.1
unnamed: R415.2, SJ125.2
unnamed: D51.C, R431.1
unnamed: D52.C, R432.1
unnamed: R440.2, S51.1
unnamed: R438.1, SJ126.2
unnamed: R430.1, SJ127.1
unnamed: R429.1, SJ128.1
unnamed: R432.2, SJ130.2
unnamed: D53.C, R448.1
unnamed: D54.C, R449.1
unnamed: R457.2, S53.1
unnamed: R455.1, SJ131.2
unnamed: R447.1, SJ132.1
unnamed: R446.1, SJ133.1
unnamed: R449.2, SJ135.2
unnamed: D55.C, R465.1
unnamed: D56.C, R466.1
unnamed: R474.2, S55.1
unnamed: R472.1, SJ136.2
unnamed: R464.1, SJ137.1
unnamed: R463.1, SJ138.1
unnamed: R466.2, SJ140.2
OUT: C3.1, D1.A, D2.A, JP7.1, JP8.2, JP9.2, R16.1, R17.1, U1.10, U1.11
OUT1: C8.1, D3.A, D4.A, JP20.1, JP21.2, JP22.2, R26.1, R27.1, U4.10, U4.11
OUT2: C13.1, D5.A, D6.A, JP33.1, JP34.2, JP35.2, R43.1, R44.1, U6.10, U6.11
OUT3: C18.1, D7.A, D8.A, JP46.1, JP47.2, JP48.2, R60.1, R61.1, U8.10, U8.11
OUT4: C23.1, D9.A, D10.A, JP59.1, JP60.2, JP61.2, R77.1, R78.1, U10.10, U10.11
OUT5: C28.1, D11.A, D12.A, JP72.1, JP73.2, JP74.2, R94.1, R95.1, U12.10, U12.11
OUT6: C33.1, D13.A, D14.A, JP85.1, JP86.2, JP87.2, R111.1, R112.1, U14.10, U14.11
OUT7: C38.1, D15.A, D16.A, JP98.1, JP99.2, JP100.2, R128.1, R129.1, U16.10, U16.11
OUT8: C43.1, D17.A, D18.A, JP111.1, JP112.2, JP113.2, R145.1, R146.1, U18.10, U18.11
OUT9: C48.1, D19.A, D20.A, JP124.1, JP125.2, JP126.2, R162.1, R163.1, U20.10, U20.11
OUT10: C53.1, D21.A, D22.A, JP137.1, JP138.2, JP139.2, R179.1, R180.1, U22.10, U22.11
OUT11: C58.1, D23.A, D24.A, JP150.1, JP151.2, JP152.2, R196.1, R197.1, U24.10, U24.11
OUT12: C63.1, D25.A, D26.A, JP163.1, JP164.2, JP165.2, R213.1, R214.1, U26.10, U26.11
OUT13: C68.1, D27.A, D28.A, JP176.1, JP177.2, JP178.2, R230.1, R231.1, U28.10, U28.11
OUT14: C73.1, D29.A, D30.A, JP189.1, JP190.2, JP191.2, R247.1, R248.1, U30.10, U30.11
OUT15: C78.1, D31.A, D32.A, JP202.1, JP203.2, JP204.2, R264.1, R265.1, U32.10, U32.11
OUT16: C83.1, D33.A, D34.A, JP215.1, JP216.2, JP217.2, R281.1, R282.1, U34.10, U34.11
OUT17: C88.1, D35.A, D36.A, JP228.1, JP229.2, JP230.2, R298.1, R299.1, U36.10, U36.11
OUT18: C93.1, D37.A, D38.A, JP241.1, JP242.2, JP243.2, R315.1, R316.1, U38.10, U38.11
OUT19: C98.1, D39.A, D40.A, JP254.1, JP255.2, JP256.2, R332.1, R333.1, U40.10, U40.11
OUT20: C103.1, D41.A, D42.A, JP267.1, JP268.2, JP269.2, R349.1, R350.1, U42.10, U42.11
OUT21: C108.1, D43.A, D44.A, JP280.1, JP281.2, JP282.2, R366.1, R367.1, U44.10, U44.11
OUT22: C113.1, D45.A, D46.A, JP293.1, JP294.2, JP295.2, R383.1, R384.1, U46.10, U46.11
OUT23: C118.1, D47.A, D48.A, JP306.1, JP307.2, JP308.2, R400.1, R401.1, U48.10, U48.11
OUT24: C123.1, D49.A, D50.A, JP319.1, JP320.2, JP321.2, R417.1, R418.1, U50.10, U50.11
OUT25: C128.1, D51.A, D52.A, JP332.1, JP333.2, JP334.2, R434.1, R435.1, U52.10, U52.11
OUT26: C133.1, D53.A, D54.A, JP345.1, JP346.2, JP347.2, R451.1, R452.1, U54.10, U54.11
OUT27: C138.1, D55.A, D56.A, JP358.1, JP359.2, JP360.2, R468.1, R469.1, U56.10, U56.11
SCL: JP10.4, R14.1, U2.2
SCL1: JP16.4, R20.1, U3.2
SCL2: JP29.4, R37.1, U5.2
SCL3: JP42.4, R54.1, U7.2
SCL4: JP55.4, R71.1, U9.2
SCL5: JP68.4, R88.1, U11.2
SCL6: JP81.4, R105.1, U13.2
SCL7: JP94.4, R122.1, U15.2
SCL8: JP107.4, R139.1, U17.2
SCL9: JP120.4, R156.1, U19.2
SCL10: JP133.4, R173.1, U21.2
SCL11: JP146.4, R190.1, U23.2
SCL12: JP159.4, R207.1, U25.2
SCL13: JP172.4, R224.1, U27.2
SCL14: JP185.4, R241.1, U29.2
SCL15: JP198.4, R258.1, U31.2
SCL16: JP211.4, R275.1, U33.2
SCL17: JP224.4, R292.1, U35.2
SCL18: JP237.4, R309.1, U37.2
SCL19: JP250.4, R326.1, U39.2
SCL20: JP263.4, R343.1, U41.2
SCL21: JP276.4, R360.1, U43.2
SCL22: JP289.4, R377.1, U45.2
SCL23: JP302.4, R394.1, U47.2
SCL24: JP315.4, R411.1, U49.2
SCL25: JP328.4, R428.1, U51.2
SCL26: JP341.4, R445.1, U53.2
SCL27: JP354.4, R462.1, U55.2
SDA: JP10.3, R13.1, U2.1
SDA1: JP16.3, R19.1, U3.1
SDA2: JP29.3, R36.1, U5.1
SDA3: JP42.3, R53.1, U7.1
SDA4: JP55.3, R70.1, U9.1
SDA5: JP68.3, R87.1, U11.1
SDA6: JP81.3, R104.1, U13.1
SDA7: JP94.3, R121.1, U15.1
SDA8: JP107.3, R138.1, U17.1
SDA9: JP120.3, R155.1, U19.1
SDA10: JP133.3, R172.1, U21.1
SDA11: JP146.3, R189.1, U23.1
SDA12: JP159.3, R206.1, U25.1
SDA13: JP172.3, R223.1, U27.1
SDA14: JP185.3, R240.1, U29.1
SDA15: JP198.3, R257.1, U31.1
SDA16: JP211.3, R274.1, U33.1
SDA17: JP224.3, R291.1, U35.1
SDA18: JP237.3, R308.1, U37.1
SDA19: JP250.3, R325.1, U39.1
SDA20: JP263.3, R342.1, U41.1
SDA21: JP276.3, R359.1, U43.1
SDA22: JP289.3, R376.1, U45.1
SDA23: JP302.3, R393.1, U47.1
SDA24: JP315.3, R410.1, U49.1
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
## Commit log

2015-12-08 Adding datasheets for BQ24075 and BQ27441-G1
2015-12-08 Initial commit of hardware.
2015-12-09 Adding a few PROD_ID's
2015-12-09 Swapping out DIP switch for larger variant
2015-12-09 Adding silk to EN pin DIP switch positions
2015-12-09 Nudging sparkfun logo
2015-12-09 Adding PROD_ID's for new components
2016-02-29 Adding SJ5, to set power LED to PWR or PGOOD.
2016-02-29 Re-arranging some silk
2016-03-04 Break out D+/D-, silkscreen fixes
2016-03-04 Small silk fixes after run through checklist
2016-03-09 Reverting version to v02 - proto round 2
2016-04-04 Moving some silk, nudging a via, upping to v10
2016-04-04 Fixing 1.8V OUT silkscreen
2016-04-04 Updating DIP switch silkscreen
2016-04-05 Increasing line width on BQ27441-G1 package.
2016-04-06 created panel v10
2016-06-23 Readme cleanup.
2016-06-23 Removing temp library, and updating libs in eagle files.
2016-06-23 Squashed 'Libraries/Arduino/' content from commit 8eda0d6
    git-subtree-dir: Libraries/Arduino
    git-subtree-split: 8eda0d6754c3a09a8a509ac4fc0d03b2e4acdd93
2016-06-23 Fixing version 1.0 link
2016-11-29 Values Added to 3 Part on .brd/.sch
    USB-AB-MICRO-SMD_V03
    SW_DIP-2_SMD
    RIGHT_ANGLE_SLIDE_SWITCH_SMD
2024-12-12 Fixes BOM for Battery Babysitter
2025-01-07 Removes unnecessary files
